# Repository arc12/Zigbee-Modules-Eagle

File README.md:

# Zigbee Modules Eagle
## E18 Simple Breakout
A simple breakout board for the Ebyte E18 MS1 "stamp" module (i.e. a version without the extra power amplifier). The device shown is the PCB variant but AFAIK the landing pattern is identical for the IPX variant. The PA1/PA2 versions of E18 include a power amplifier and have a slightly larger landing pattern which probably won't fit (try at your own risk!).

This is "simple" in that the main use case is to plug into breadboard; although there are some components other than the E18 on the board, these are included for possible convenience (and using available board space).

Some notes on motivation, layout pragmatics, and options:
- The long header is meant to be populated with right-angle pins. This will put the antenna nicely up and leaves plenty of space for other components on the breadboard (I find the breakouts with very wide dual-in-line pin-outs to be rather irritating, and Arduino style sockets and flying leads are not great when more than a few connections are to be made).
- The 5 pin header is for firmware flashing. I opted for this, rather than the full 10 pin "debug" header which CCDebugger uses, for econonmy of space. These 5 pins are quite sufficient for using CCDebugger with TI SmartRF Flash Programmer (I made a little adapter) or if using something like https://github.com/jmichault/flash_cc2531 (or my patched version for use with Pi v1 GPIOs at https://github.com/arc12/flash_cc2531).
- The 4 pin header may be convenient for either UART or I2C connections. I'm expecting to be using PTVO and for the CC2530 it fixes UART pins to be P0.2 and P0.3. This header is meant to be mounted on the same side as the E18 module (opposite to switches).
- The switches should be configured using the solder jumpers.
  - SJ1 handles the "Reset" button: A connects to E18 Reset; B connects to P0.0.
  - SJ2 handles the "Key" button: A connects to P0.1; B connects to P1.7 (which is used by the E18 factory firmware).
- The on-board LEDs (and the enabling jumpers) should visually correlate with the pins they are connected to: P0.4, P0.5, and P2.0. These are NOT the same as used by the factory firmware. P2.0 LED has no enabling jumper.

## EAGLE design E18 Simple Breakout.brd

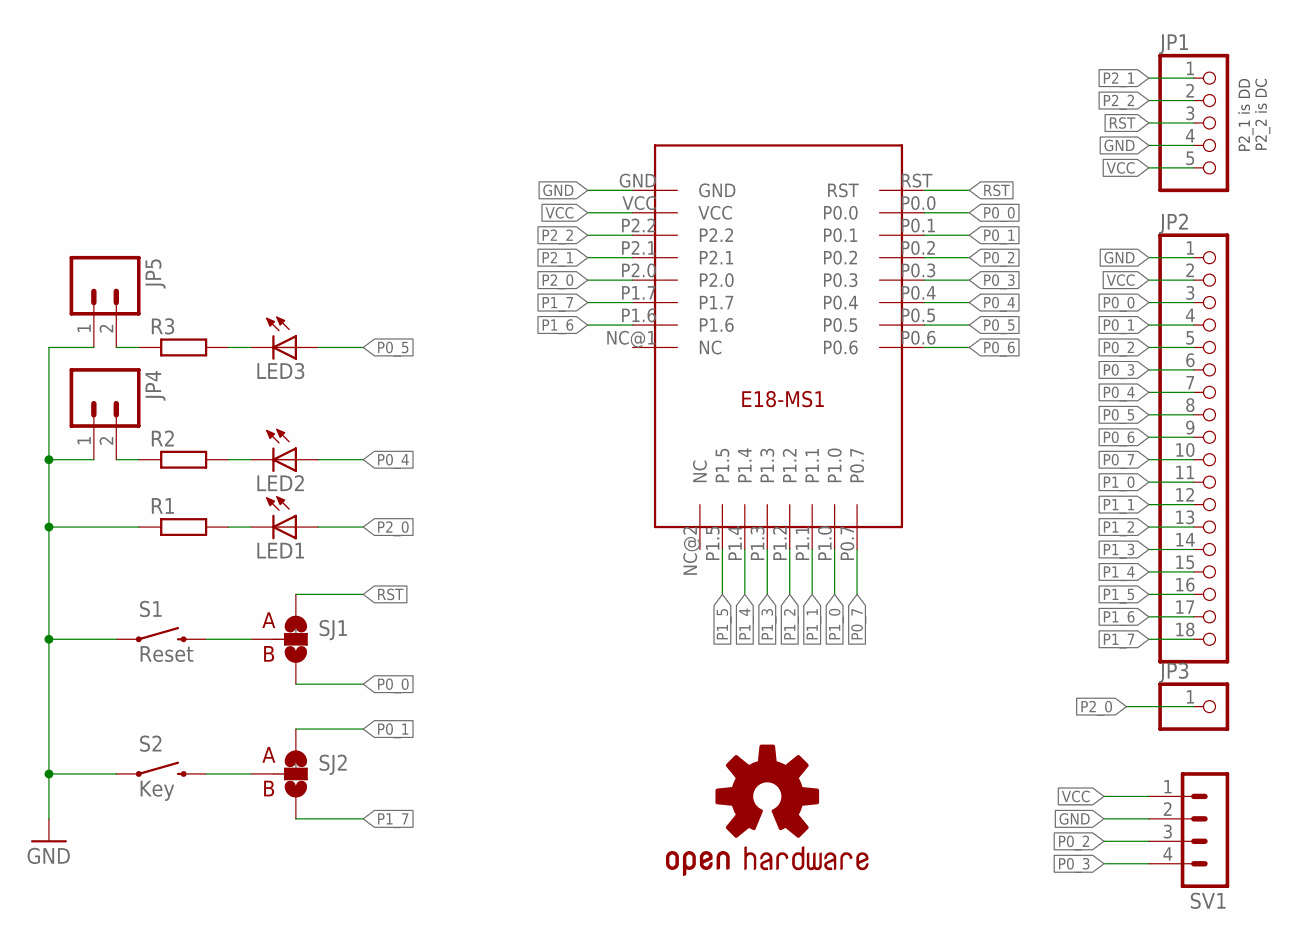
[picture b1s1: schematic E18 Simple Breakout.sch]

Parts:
JP1: PINHD-1X5; 1X05
JP2: PINHD-1X18; 1X18
JP3: PINHD-1X1; 1X01
JP4, JP5: HEADER-1X2P1X02_NO_SILK; 1X02_NO_SILK
LED1, LED2, LED3: LED1206; LED-1206
LOGO1: OSHW-LOGOM; OSHW-LOGO-M
R1, R2, R3: R-EU_; 1206
S1: Reset; TACTILE-PTH
S2: Key; TACTILE-PTH
SJ1, SJ2: SOLDERJUMPER_2WAYT; SJ_2
SV1: HEADER-1X4P; MA04-1
U$1: E18-MS1PCB; E18-MS1-PCB

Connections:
GND: JP1.4, JP2.1, JP4.1, JP5.1, R1.1, S1.1, S2.1, SV1.2, U$1.GND
unnamed: LED3.C, R3.2
unnamed: S1.3 (2), SJ1.2
unnamed: JP4.2, R2.1
unnamed: JP5.2, R3.1
unnamed: S2.3 (2), SJ2.2
unnamed: LED2.C, R2.2
unnamed: LED1.C, R1.2
P0_0: JP2.3, SJ1.3, U$1.P0.0
P0_1: JP2.4, SJ2.1, U$1.P0.1
P0_2: JP2.5, SV1.3, U$1.P0.2
P0_3: JP2.6, SV1.4, U$1.P0.3
P0_4: JP2.7, LED2.A, U$1.P0.4
P0_5: JP2.8, LED3.A, U$1.P0.5
P0_6: JP2.9, U$1.P0.6
P0_7: JP2.10, U$1.P0.7
P1_0: JP2.11, U$1.P1.0
P1_1: JP2.12, U$1.P1.1
P1_2: JP2.13, U$1.P1.2
P1_3: JP2.14, U$1.P1.3
P1_4: JP2.15, U$1.P1.4
P1_5: JP2.16, U$1.P1.5
P1_6: JP2.17, U$1.P1.6
P1_7: JP2.18, SJ2.3, U$1.P1.7
P2_0: JP3.1, LED1.A, U$1.P2.0
P2_1: JP1.1, U$1.P2.1
P2_2: JP1.2, U$1.P2.2
RST: JP1.3, SJ1.1, U$1.RST
VCC: JP1.5, JP2.2, SV1.1, U$1.VCC

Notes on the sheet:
P2_1 is DD P2_2 is DC

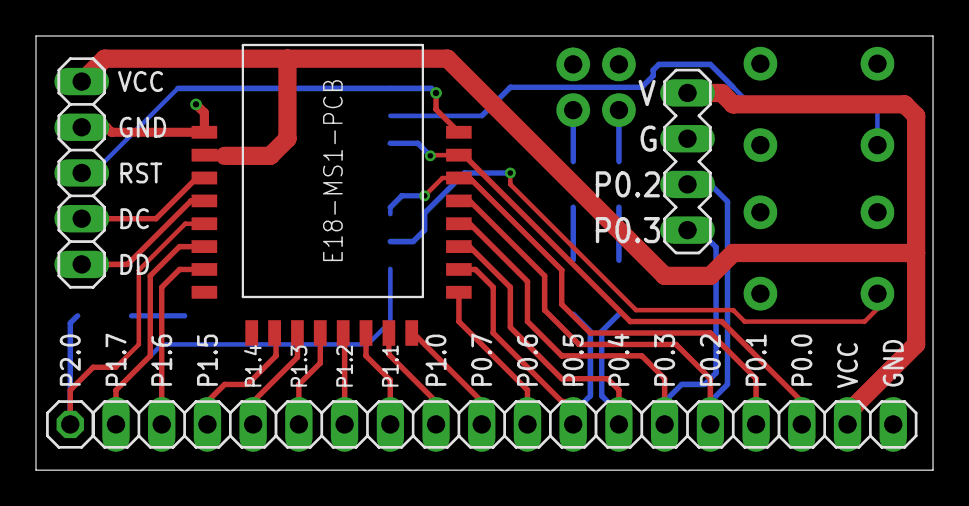
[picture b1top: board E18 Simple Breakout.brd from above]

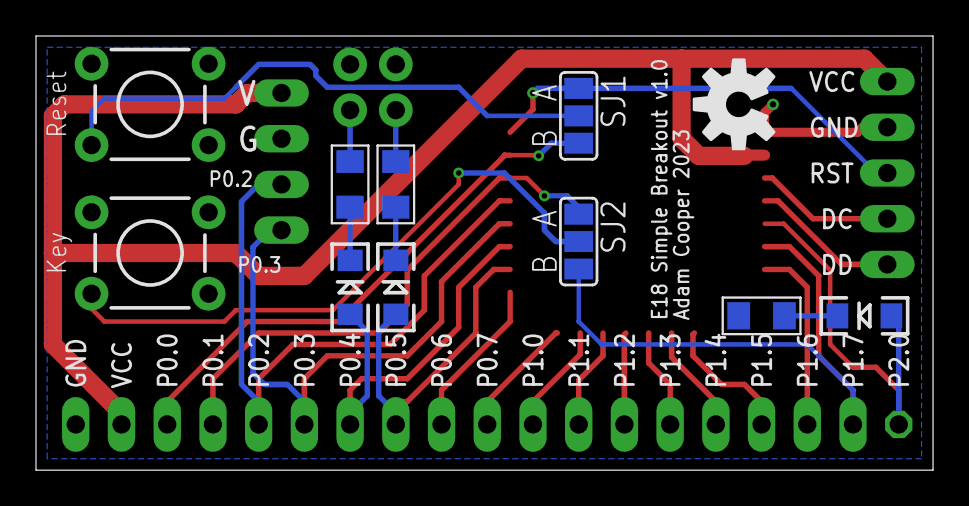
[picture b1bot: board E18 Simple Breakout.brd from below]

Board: 2 copper layers, 49.8 x 24.1 mm, 18 parts (11 on the bottom side), 29 nets.

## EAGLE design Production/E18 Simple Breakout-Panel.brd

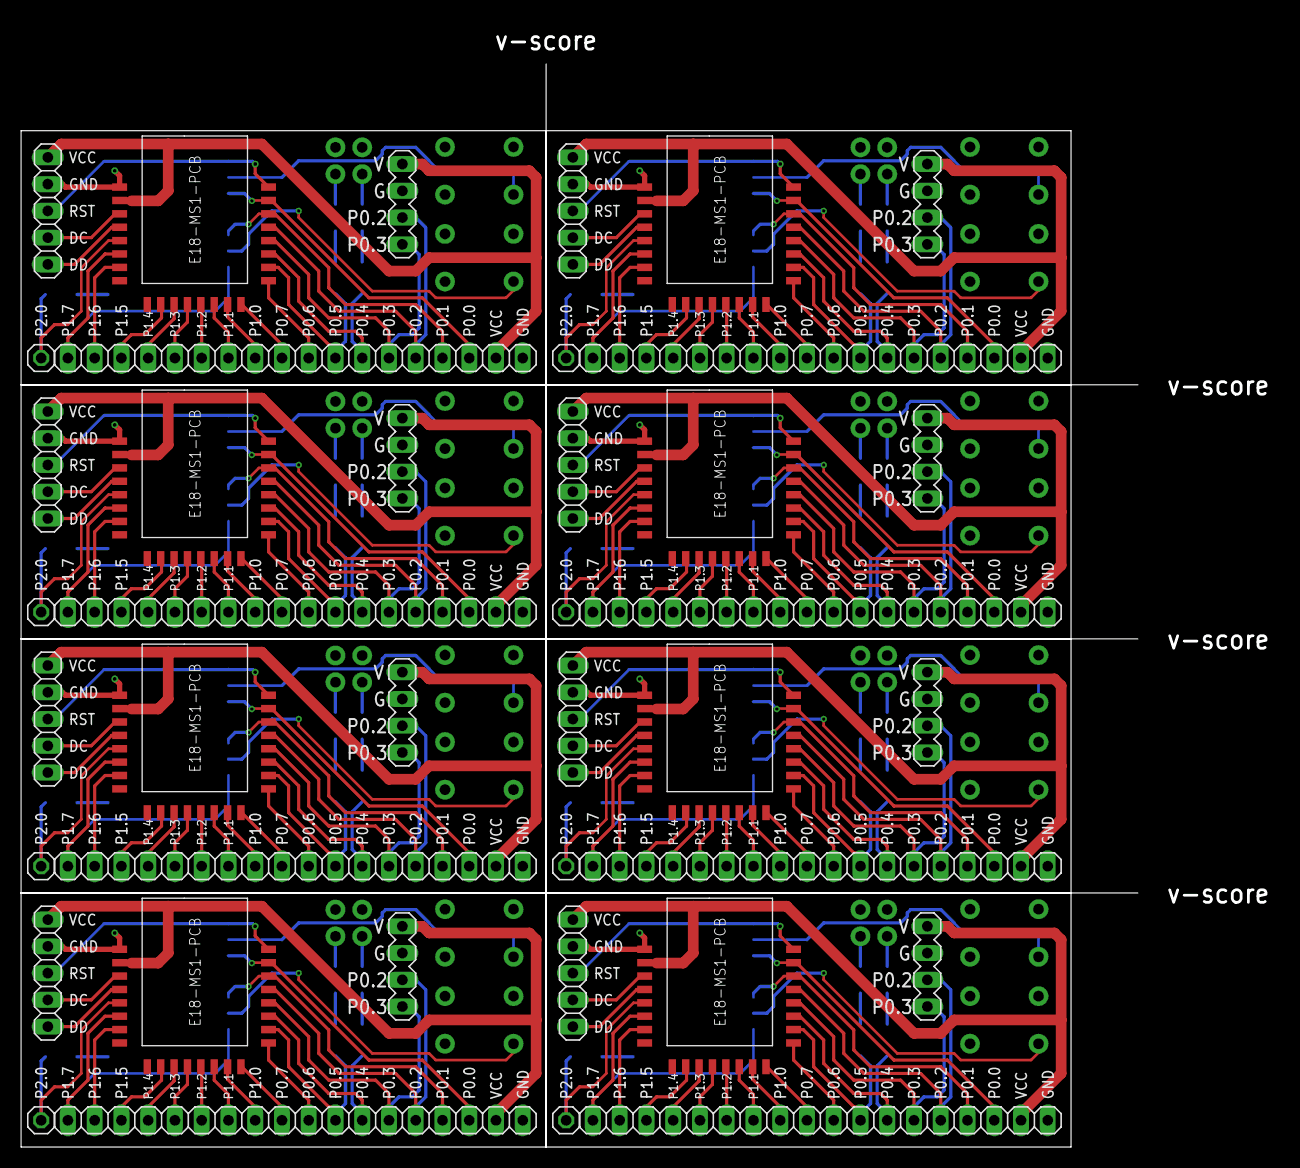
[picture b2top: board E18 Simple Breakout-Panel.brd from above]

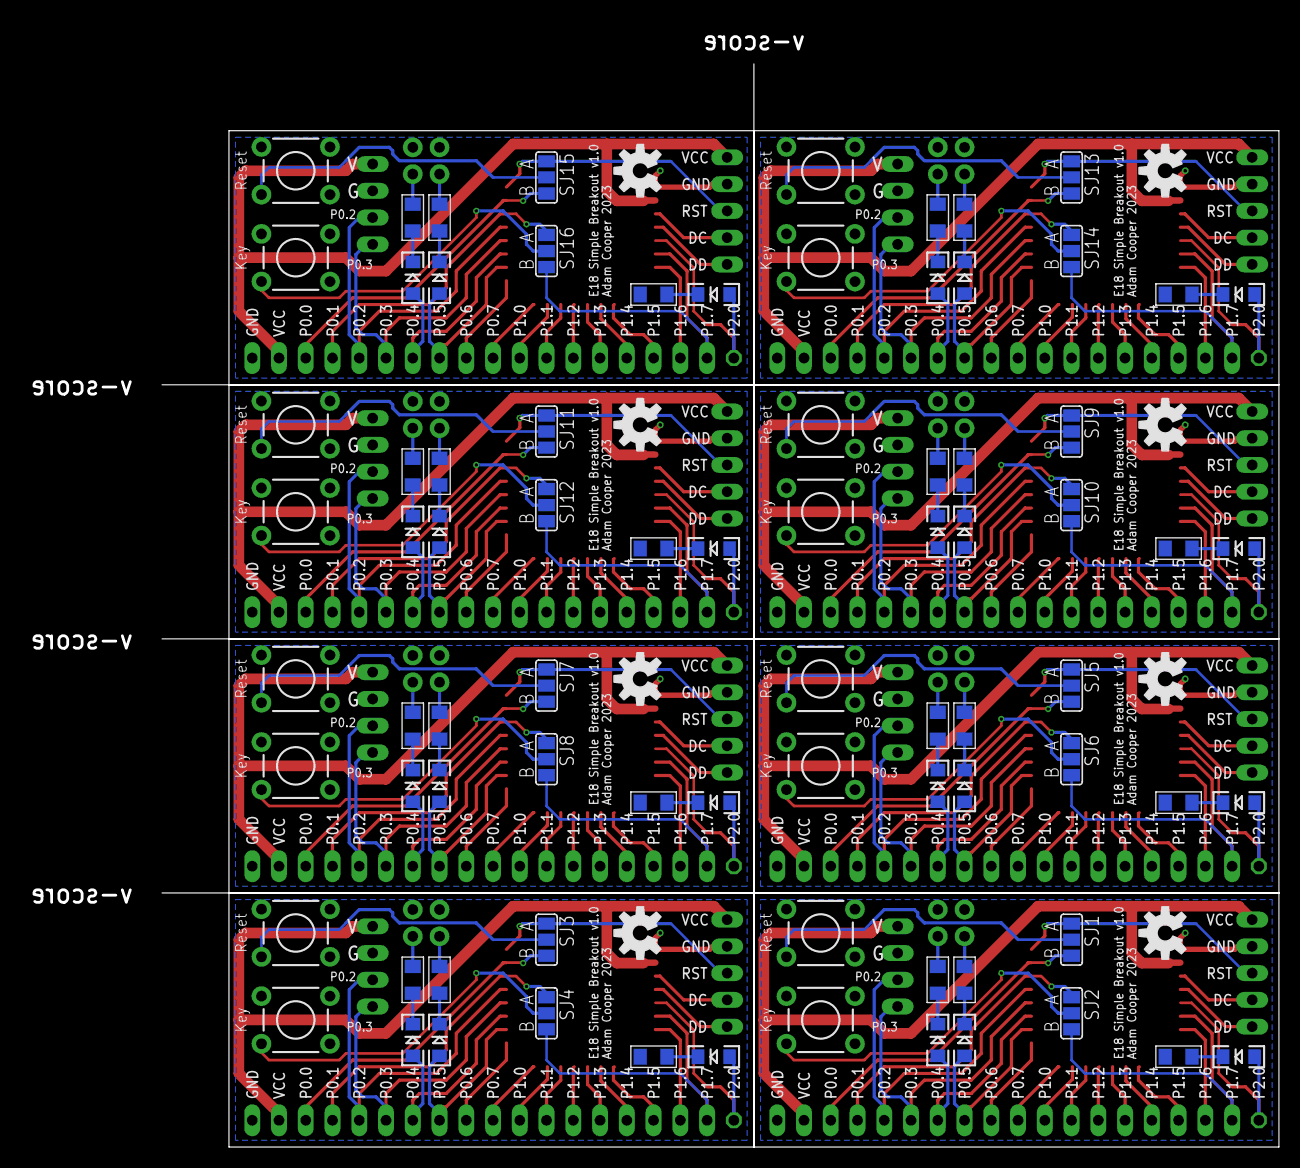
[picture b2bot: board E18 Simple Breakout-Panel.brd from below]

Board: 2 copper layers, 106.0 x 102.8 mm, 144 parts (88 on the bottom side), 232 nets.

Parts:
JP1, JP6, JP11, JP16, JP21, JP26, JP31, JP36: 1X05
JP2, JP8, JP13, JP18, JP23, JP28, JP33, JP38: 1X18
JP3, JP7, JP12, JP17, JP22, JP27, JP32, JP37: 1X01
JP4, JP5, JP9, JP10, JP14, JP15, JP19, JP20, JP24, JP25, JP29, JP30, JP34, JP35, JP39, JP40: 1X02_NO_SILK
LED1, LED2, LED3, LED4, LED5, LED6, LED7, LED8, LED9, LED10, LED11, LED12, LED13, LED14, LED15, LED16, LED17, LED18, LED19, LED20, LED21, LED22, LED23, LED24: LED-1206
LOGO1, LOGO2, LOGO3, LOGO4, LOGO5, LOGO6, LOGO7, LOGO8: OSHW-LOGOM; OSHW-LOGO-M
R1, R2, R3, R4, R5, R6, R7, R8, R9, R10, R11, R12, R13, R14, R15, R16, R17, R18, R19, R20, R21, R22, R23, R24: 1206
S1, S3, S5, S7, S9, S11, S13, S15: Reset; TACTILE-PTH
S2, S4, S6, S8, S10, S12, S14, S16: Key; TACTILE-PTH
SJ1, SJ2, SJ3, SJ4, SJ5, SJ6, SJ7, SJ8, SJ9, SJ10, SJ11, SJ12, SJ13, SJ14, SJ15, SJ16: SJ_2
SV1, SV2, SV3, SV4, SV5, SV6, SV7, SV8: MA04-1
U$1, U$2, U$3, U$4, U$5, U$6, U$7, U$8: E18-MS1PCB; E18-MS1-PCB

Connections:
GND: JP1.4, JP2.1, JP4.1, JP5.1, R1.1, S1.1, S2.1, SV1.2, U$1.GND
GND1: JP6.4, JP8.1, JP9.1, JP10.1, R4.1, S3.1, S4.1, SV2.2, U$2.GND
GND2: JP11.4, JP13.1, JP14.1, JP15.1, R7.1, S5.1, S6.1, SV3.2, U$3.GND
GND3: JP16.4, JP18.1, JP19.1, JP20.1, R10.1, S7.1, S8.1, SV4.2, U$4.GND
GND4: JP21.4, JP23.1, JP24.1, JP25.1, R13.1, S9.1, S10.1, SV5.2, U$5.GND
GND5: JP26.4, JP28.1, JP29.1, JP30.1, R16.1, S11.1, S12.1, SV6.2, U$6.GND
GND6: JP31.4, JP33.1, JP34.1, JP35.1, R19.1, S13.1, S14.1, SV7.2, U$7.GND
GND7: JP36.4, JP38.1, JP39.1, JP40.1, R22.1, S15.1, S16.1, SV8.2, U$8.GND
unnamed: LED3.C, R3.2
unnamed: S1.3, SJ1.2
unnamed: JP4.2, R2.1
unnamed: JP5.2, R3.1
unnamed: S2.3, SJ2.2
unnamed: LED2.C, R2.2
unnamed: LED1.C, R1.2
unnamed: S3.3, SJ3.2
unnamed: JP9.2, R5.1
unnamed: JP10.2, R6.1
unnamed: S4.3, SJ4.2
unnamed: LED6.C, R6.2
unnamed: LED5.C, R5.2
unnamed: LED4.C, R4.2
unnamed: S5.3, SJ5.2
unnamed: JP14.2, R8.1
unnamed: JP15.2, R9.1
unnamed: S6.3, SJ6.2
unnamed: LED9.C, R9.2
unnamed: LED8.C, R8.2
unnamed: LED7.C, R7.2
unnamed: S7.3, SJ7.2
unnamed: JP19.2, R11.1
unnamed: JP20.2, R12.1
unnamed: S8.3, SJ8.2
unnamed: LED12.C, R12.2
unnamed: LED11.C, R11.2
unnamed: LED10.C, R10.2
unnamed: S9.3, SJ9.2
unnamed: JP24.2, R14.1
unnamed: JP25.2, R15.1
unnamed: S10.3, SJ10.2
unnamed: LED15.C, R15.2
unnamed: LED14.C, R14.2
unnamed: LED13.C, R13.2
unnamed: S11.3, SJ11.2
unnamed: JP29.2, R17.1
unnamed: JP30.2, R18.1
unnamed: S12.3, SJ12.2
unnamed: LED18.C, R18.2
unnamed: LED17.C, R17.2
unnamed: LED16.C, R16.2
unnamed: S13.3, SJ13.2
unnamed: JP34.2, R20.1
unnamed: JP35.2, R21.1
unnamed: S14.3, SJ14.2
unnamed: LED21.C, R21.2
unnamed: LED20.C, R20.2
unnamed: LED19.C, R19.2
unnamed: S15.3, SJ15.2
unnamed: JP39.2, R23.1
unnamed: JP40.2, R24.1
unnamed: S16.3, SJ16.2
unnamed: LED24.C, R24.2
unnamed: LED23.C, R23.2
unnamed: LED22.C, R22.2
P0_0: JP2.3, SJ1.3, U$1.P0.0
P0_1: JP2.4, SJ2.1, U$1.P0.1
P0_2: JP2.5, SV1.3, U$1.P0.2
P0_3: JP2.6, SV1.4, U$1.P0.3
P0_4: JP2.7, LED2.A, U$1.P0.4
P0_5: JP2.8, LED3.A, U$1.P0.5
P0_6: JP2.9, U$1.P0.6
P0_7: JP2.10, U$1.P0.7
P0_8: JP8.3, SJ3.3, U$2.P0.0
P0_9: JP8.4, SJ4.1, U$2.P0.1
P0_10: JP8.5, SV2.3, U$2.P0.2
P0_11: JP8.6, SV2.4, U$2.P0.3
P0_12: JP8.7, LED5.A, U$2.P0.4
P0_13: JP8.8, LED6.A, U$2.P0.5
P0_14: JP8.9, U$2.P0.6
P0_15: JP8.10, U$2.P0.7
P0_16: JP13.3, SJ5.3, U$3.P0.0
P0_17: JP13.4, SJ6.1, U$3.P0.1
P0_18: JP13.5, SV3.3, U$3.P0.2
P0_19: JP13.6, SV3.4, U$3.P0.3
P0_20: JP13.7, LED8.A, U$3.P0.4
P0_21: JP13.8, LED9.A, U$3.P0.5
P0_22: JP13.9, U$3.P0.6
P0_23: JP13.10, U$3.P0.7
P0_24: JP18.3, SJ7.3, U$4.P0.0
P0_25: JP18.4, SJ8.1, U$4.P0.1
P0_26: JP18.5, SV4.3, U$4.P0.2
P0_27: JP18.6, SV4.4, U$4.P0.3
P0_28: JP18.7, LED11.A, U$4.P0.4
P0_29: JP18.8, LED12.A, U$4.P0.5
P0_30: JP18.9, U$4.P0.6
P0_31: JP18.10, U$4.P0.7
P0_32: JP23.3, SJ9.3, U$5.P0.0
P0_33: JP23.4, SJ10.1, U$5.P0.1
P0_34: JP23.5, SV5.3, U$5.P0.2
P0_35: JP23.6, SV5.4, U$5.P0.3
P0_36: JP23.7, LED14.A, U$5.P0.4
P0_37: JP23.8, LED15.A, U$5.P0.5
P0_38: JP23.9, U$5.P0.6
P0_39: JP23.10, U$5.P0.7
P0_40: JP28.3, SJ11.3, U$6.P0.0
P0_41: JP28.4, SJ12.1, U$6.P0.1
P0_42: JP28.5, SV6.3, U$6.P0.2
P0_43: JP28.6, SV6.4, U$6.P0.3
P0_44: JP28.7, LED17.A, U$6.P0.4
P0_45: JP28.8, LED18.A, U$6.P0.5
P0_46: JP28.9, U$6.P0.6
P0_47: JP28.10, U$6.P0.7
P0_48: JP33.3, SJ13.3, U$7.P0.0
P0_49: JP33.4, SJ14.1, U$7.P0.1
P0_50: JP33.5, SV7.3, U$7.P0.2
P0_51: JP33.6, SV7.4, U$7.P0.3
P0_52: JP33.7, LED20.A, U$7.P0.4
P0_53: JP33.8, LED21.A, U$7.P0.5
P0_54: JP33.9, U$7.P0.6
P0_55: JP33.10, U$7.P0.7
P0_56: JP38.3, SJ15.3, U$8.P0.0
P0_57: JP38.4, SJ16.1, U$8.P0.1
P0_58: JP38.5, SV8.3, U$8.P0.2
P0_59: JP38.6, SV8.4, U$8.P0.3
P0_60: JP38.7, LED23.A, U$8.P0.4
P0_61: JP38.8, LED24.A, U$8.P0.5
P0_62: JP38.9, U$8.P0.6
P0_63: JP38.10, U$8.P0.7
P1_0: JP2.11, U$1.P1.0
P1_1: JP2.12, U$1.P1.1
P1_2: JP2.13, U$1.P1.2
P1_3: JP2.14, U$1.P1.3
P1_4: JP2.15, U$1.P1.4
P1_5: JP2.16, U$1.P1.5
P1_6: JP2.17, U$1.P1.6
P1_7: JP2.18, SJ2.3, U$1.P1.7
P1_8: JP8.18, SJ4.3, U$2.P1.7
P1_9: JP8.17, U$2.P1.6
P1_10: JP8.16, U$2.P1.5
P1_11: JP8.15, U$2.P1.4
P1_12: JP8.14, U$2.P1.3
P1_13: JP8.13, U$2.P1.2
P1_14: JP8.12, U$2.P1.1
P1_15: JP8.11, U$2.P1.0
P1_16: JP13.18, SJ6.3, U$3.P1.7
P1_17: JP13.17, U$3.P1.6
P1_18: JP13.16, U$3.P1.5
P1_19: JP13.15, U$3.P1.4
P1_20: JP13.14, U$3.P1.3
P1_21: JP13.13, U$3.P1.2
P1_22: JP13.12, U$3.P1.1
P1_23: JP13.11, U$3.P1.0
P1_24: JP18.18, SJ8.3, U$4.P1.7
P1_25: JP18.17, U$4.P1.6
P1_26: JP18.16, U$4.P1.5
P1_27: JP18.15, U$4.P1.4
P1_28: JP18.14, U$4.P1.3
P1_29: JP18.13, U$4.P1.2
P1_30: JP18.12, U$4.P1.1
P1_31: JP18.11, U$4.P1.0
P1_32: JP23.18, SJ10.3, U$5.P1.7
P1_33: JP23.17, U$5.P1.6
P1_34: JP23.16, U$5.P1.5
P1_35: JP23.15, U$5.P1.4
P1_36: JP23.14, U$5.P1.3
P1_37: JP23.13, U$5.P1.2
P1_38: JP23.12, U$5.P1.1
P1_39: JP23.11, U$5.P1.0
P1_40: JP28.18, SJ12.3, U$6.P1.7
P1_41: JP28.17, U$6.P1.6
P1_42: JP28.16, U$6.P1.5
P1_43: JP28.15, U$6.P1.4
P1_44: JP28.14, U$6.P1.3
P1_45: JP28.13, U$6.P1.2
P1_46: JP28.12, U$6.P1.1
P1_47: JP28.11, U$6.P1.0
P1_48: JP33.18, SJ14.3, U$7.P1.7
P1_49: JP33.17, U$7.P1.6
P1_50: JP33.16, U$7.P1.5
P1_51: JP33.15, U$7.P1.4
P1_52: JP33.14, U$7.P1.3
P1_53: JP33.13, U$7.P1.2
P1_54: JP33.12, U$7.P1.1
P1_55: JP33.11, U$7.P1.0
P1_56: JP38.18, SJ16.3, U$8.P1.7
P1_57: JP38.17, U$8.P1.6
P1_58: JP38.16, U$8.P1.5
P1_59: JP38.15, U$8.P1.4
P1_60: JP38.14, U$8.P1.3
P1_61: JP38.13, U$8.P1.2
P1_62: JP38.12, U$8.P1.1
P1_63: JP38.11, U$8.P1.0
P2_0: JP3.1, LED1.A, U$1.P2.0
P2_1: JP1.1, U$1.P2.1
P2_2: JP1.2, U$1.P2.2
P2_3: JP6.2, U$2.P2.2
P2_4: JP6.1, U$2.P2.1
P2_5: JP7.1, LED4.A, U$2.P2.0
P2_6: JP11.2, U$3.P2.2
P2_7: JP11.1, U$3.P2.1
P2_8: JP12.1, LED7.A, U$3.P2.0
P2_9: JP16.2, U$4.P2.2
P2_10: JP16.1, U$4.P2.1
P2_11: JP17.1, LED10.A, U$4.P2.0
P2_12: JP21.2, U$5.P2.2
P2_13: JP21.1, U$5.P2.1
P2_14: JP22.1, LED13.A, U$5.P2.0
P2_15: JP26.2, U$6.P2.2
P2_16: JP26.1, U$6.P2.1
P2_17: JP27.1, LED16.A, U$6.P2.0
P2_18: JP31.2, U$7.P2.2
P2_19: JP31.1, U$7.P2.1
P2_20: JP32.1, LED19.A, U$7.P2.0
P2_21: JP36.2, U$8.P2.2
P2_22: JP36.1, U$8.P2.1
P2_23: JP37.1, LED22.A, U$8.P2.0
RST: JP1.3, SJ1.1, U$1.RST
RST1: JP6.3, SJ3.1, U$2.RST
RST2: JP11.3, SJ5.1, U$3.RST
RST3: JP16.3, SJ7.1, U$4.RST
RST4: JP21.3, SJ9.1, U$5.RST
RST5: JP26.3, SJ11.1, U$6.RST
RST6: JP31.3, SJ13.1, U$7.RST
RST7: JP36.3, SJ15.1, U$8.RST
VCC: JP1.5, JP2.2, SV1.1, U$1.VCC
VCC1: JP6.5, JP8.2, SV2.1, U$2.VCC
VCC2: JP11.5, JP13.2, SV3.1, U$3.VCC
VCC3: JP16.5, JP18.2, SV4.1, U$4.VCC
VCC4: JP21.5, JP23.2, SV5.1, U$5.VCC
VCC5: JP26.5, JP28.2, SV6.1, U$6.VCC
VCC6: JP31.5, JP33.2, SV7.1, U$7.VCC
VCC7: JP36.5, JP38.2, SV8.1, U$8.VCC

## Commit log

2023-07-05 provisional v1.0 unpanelised
2023-07-05 fix layer so panelisation works. incidentally now include the layers 122 and 126 from Tools > Panelize
2023-07-05 add panelised board
2023-07-05 add a bit of readme
2023-07-05 Update README.md
    formatting list
2023-07-26 Add pictures
2023-07-26 amend readme
2025-03-23 add pdf of schematic
